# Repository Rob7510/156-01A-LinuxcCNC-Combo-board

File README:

Note: First version, in test.

This board can drive in LinuxCNC a 3-axis CNC over a single printer port set to default(out/epp) mode,
and provides 4 (pin 10-13) + 16 signal inputs and 9 (pin 1-9) + 16 output signals using the integrated
LSRIO16 softwaare multiplexer.

The X, Y, Z axis and A (or two other signals instead of A) are not isolated from the PC,
they connect to stepper drivers that are normally floating.
The remaining 20 input and 16 output signals are electrically isolated from the PC.

Combo port example configuration:

Pin Output Signal
1   Enable
2   X step
3   X dir
4   Y step
5   Y dir
6   Z step
7   Z dir
8   Spindle  etc
9   Aux out
14  LSRIO16 output (fixed onboard)
16  LSRIO16 clock (fixed onboard)
17  LSRIO16 data latch (fixed onboard)

Pin Input signal
10  X home
11  Y home
12  Z home
13  Probe
15  LSRIO16 input (fixed onboard)

All other signals (eg limits, ext_estop, buttons, lights) can be handled by the 16 in and 16
output signals of the LSRIO16 multimplexer with a polling delay of max 300 msec.

LSRIO16 fixed signal connections 
RCLK   <- SRIO-DATA_LATCH (P17)
SRCLK  <- SRIO-CLOCK-OUTPUT (P16)
DT-OUT -> LSRIO-INPUT-STREAM (P15)
DT-IN  <- SRIO-OUTPUT-STREAM (P14)
SRLD = inverted RCLK

Test software to set outputs and read inputs: mx16_test.hal, mx16_test.xml

updated 2024-10-17

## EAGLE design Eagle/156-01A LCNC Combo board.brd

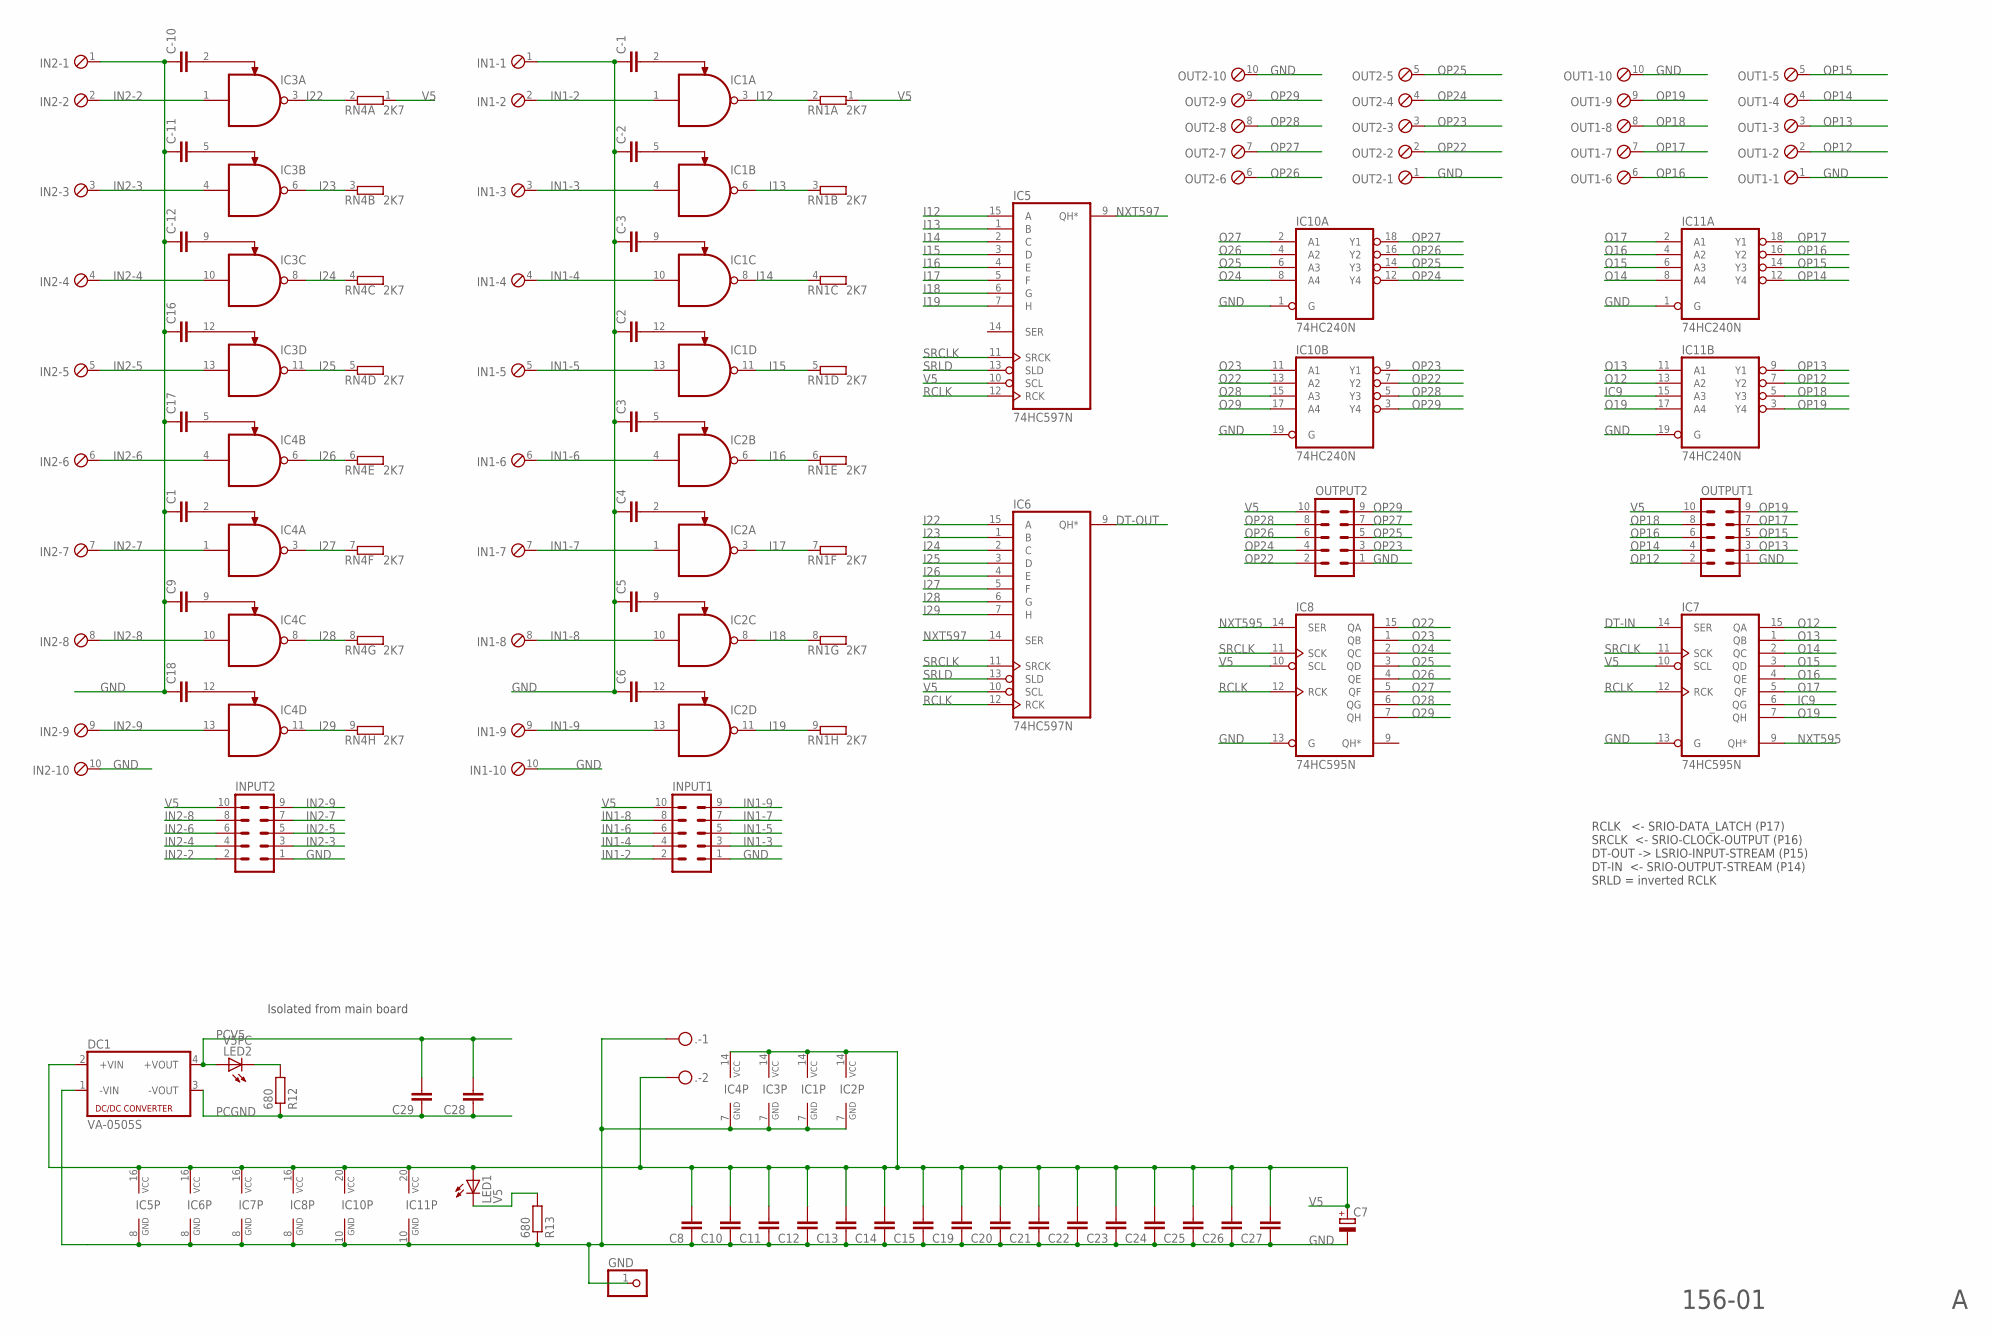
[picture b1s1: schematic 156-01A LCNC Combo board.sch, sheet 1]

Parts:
.: MKDSN1,5/2-5,08
C1, C2, C3, C4, C5, C6, C8, C9, C10, C11, C12, C13, C14, C15, C16, C17, C18, C19, C20, C21, C22, C23, C24, C25, C26, C27, C28, C29: C-EU025-024X044; C025-024X044
C7: CPOL-EUE3.5-8; E3,5-8
C-1, C-2, C-3, C-10, C-11, C-12: C-EU025-024X044; C025-024X044
DC1: VA-0505S; 4SIL
GND: PINHD-1X1; 1X01
IC1, IC2, IC3, IC4: MC1489DIP; DIL14
IC5, IC6: 74HC597N; DIL16
IC7, IC8: 74HC595N; DIL16
IC10, IC11: 74HC240N; DIL20
IN1, IN2: MPT10; 10POL254
INPUT1, INPUT2: ML10
LED1: V5; LED3MM
LED2: V5PC; LED3MM
OUT1, OUT2: MPT10; 10POL254
OUTPUT1, OUTPUT2: ML10
R12, R13: 680; 0207/10
RN1, RN4: 2K7; SIL9

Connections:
DT-IN: IC7.14 (SER); also elsewhere on the board
DT-OUT: IC6.9 (QH*); also elsewhere on the board
GND: ..1, C1.1, C2.1, C3.1, C4.1, C5.1, C6.1, C7.-, C8.1, C9.1, C10.1, C11.1, C12.1, C13.1, C14.1, C15.1, C16.1, C17.1, C18.1, C19.1, C20.1, C21.1, C22.1, C23.1, C24.1, C25.1, C26.1, C27.1, C-1.1, C-2.1, C-3.1, C-10.1, C-11.1, C-12.1, DC1.1 (-VIN), GND.1, IC1.7 (GND), IC2.7 (GND), IC3.7 (GND), IC4.7 (GND), IC5.8 (GND), IC6.8 (GND), IC7.8 (GND), IC7.13 (G), IC8.8 (GND), IC8.13 (G), IC10.1 (G), IC10.10 (GND), IC10.19 (G), IC11.1 (G), IC11.10 (GND), IC11.19 (G), IN1.1, IN1.10, IN2.1, IN2.10, INPUT1.1, INPUT2.1, OUT1.1, OUT1.10, OUT2.1, OUT2.10, OUTPUT1.1, OUTPUT2.1, R13.1; also elsewhere on the board
I12: IC1.3 (O), IC5.15 (A), RN1.2
I13: IC1.6 (O), IC5.1 (B), RN1.3 (2)
I14: IC1.8 (O), IC5.2 (C), RN1.4 (2)
I15: IC1.11 (O), IC5.3 (D), RN1.5 (2)
I16: IC2.6 (O), IC5.4 (E), RN1.6 (2)
I17: IC2.3 (O), IC5.5 (F), RN1.7 (2)
I18: IC2.8 (O), IC5.6 (G), RN1.8 (2)
I19: IC2.11 (O), IC5.7 (H), RN1.9 (2)
I22: IC3.3 (O), IC6.15 (A), RN4.2
I23: IC3.6 (O), IC6.1 (B), RN4.3 (2)
I24: IC3.8 (O), IC6.2 (C), RN4.4 (2)
I25: IC3.11 (O), IC6.3 (D), RN4.5 (2)
I26: IC4.6 (O), IC6.4 (E), RN4.6 (2)
I27: IC4.3 (O), IC6.5 (F), RN4.7 (2)
I28: IC4.8 (O), IC6.6 (G), RN4.8 (2)
I29: IC4.11 (O), IC6.7 (H), RN4.9 (2)
IC9: IC7.6 (QG), IC11.15 (A3)
IN1-2: IC1.1 (I0), IN1.2, INPUT1.2
IN1-3: IC1.4 (I0), IN1.3, INPUT1.3
IN1-4: IC1.10 (I0), IN1.4, INPUT1.4
IN1-5: IC1.13 (I0), IN1.5, INPUT1.5
IN1-6: IC2.4 (I0), IN1.6, INPUT1.6
IN1-7: IC2.1 (I0), IN1.7, INPUT1.7
IN1-8: IC2.10 (I0), IN1.8, INPUT1.8
IN1-9: IC2.13 (I0), IN1.9, INPUT1.9
IN2-2: IC3.1 (I0), IN2.2, INPUT2.2
IN2-3: IC3.4 (I0), IN2.3, INPUT2.3
IN2-4: IC3.10 (I0), IN2.4, INPUT2.4
IN2-5: IC3.13 (I0), IN2.5, INPUT2.5
IN2-6: IC4.4 (I0), IN2.6, INPUT2.6
IN2-7: IC4.1 (I0), IN2.7, INPUT2.7
IN2-8: IC4.10 (I0), IN2.8, INPUT2.8
IN2-9: IC4.13 (I0), IN2.9, INPUT2.9
unnamed: C-2.2, IC1.5 (I1)
unnamed: C-10.2, IC3.2 (I1)
unnamed: C17.2, IC4.5 (I1)
unnamed: C-3.2, IC1.9 (I1)
unnamed: C1.2, IC4.2 (I1)
unnamed: C9.2, IC4.9 (I1)
unnamed: C18.2, IC4.12 (I1)
unnamed: C2.2, IC1.12 (I1)
unnamed: C4.2, IC2.2 (I1)
unnamed: C5.2, IC2.9 (I1)
unnamed: C6.2, IC2.12 (I1)
unnamed: C-1.2, IC1.2 (I1)
unnamed: C3.2, IC2.5 (I1)
unnamed: LED2.K (C), R12.2
unnamed: LED1.K (C), R13.2
unnamed: C-11.2, IC3.5 (I1)
unnamed: C-12.2, IC3.9 (I1)
unnamed: C16.2, IC3.12 (I1)
NXT595: IC7.9 (QH*), IC8.14 (SER)
NXT597: IC5.9 (QH*), IC6.14 (SER)
O12: IC7.15 (QA), IC11.13 (A2)
O13: IC7.1 (QB), IC11.11 (A1)
O14: IC7.2 (QC), IC11.8 (A4)
O15: IC7.3 (QD), IC11.6 (A3)
O16: IC7.4 (QE), IC11.4 (A2)
O17: IC7.5 (QF), IC11.2 (A1)
O19: IC7.7 (QH), IC11.17 (A4)
O22: IC8.15 (QA), IC10.13 (A2)
O23: IC8.1 (QB), IC10.11 (A1)
O24: IC8.2 (QC), IC10.8 (A4)
O25: IC8.3 (QD), IC10.6 (A3)
O26: IC8.4 (QE), IC10.4 (A2)
O27: IC8.5 (QF), IC10.2 (A1)
O28: IC8.6 (QG), IC10.15 (A3)
O29: IC8.7 (QH), IC10.17 (A4)
OP12: IC11.7 (Y2), OUT1.2, OUTPUT1.2
OP13: IC11.9 (Y1), OUT1.3, OUTPUT1.3
OP14: IC11.12 (Y4), OUT1.4, OUTPUT1.4
OP15: IC11.14 (Y3), OUT1.5, OUTPUT1.5
OP16: IC11.16 (Y2), OUT1.6, OUTPUT1.6
OP17: IC11.18 (Y1), OUT1.7, OUTPUT1.7
OP18: IC11.5 (Y3), OUT1.8, OUTPUT1.8
OP19: IC11.3 (Y4), OUT1.9, OUTPUT1.9
OP22: IC10.7 (Y2), OUT2.2, OUTPUT2.2
OP23: IC10.9 (Y1), OUT2.3, OUTPUT2.3
OP24: IC10.12 (Y4), OUT2.4, OUTPUT2.4
OP25: IC10.14 (Y3), OUT2.5, OUTPUT2.5
OP26: IC10.16 (Y2), OUT2.6, OUTPUT2.6
OP27: IC10.18 (Y1), OUT2.7, OUTPUT2.7
OP28: IC10.5 (Y3), OUT2.8, OUTPUT2.8
OP29: IC10.3 (Y4), OUT2.9, OUTPUT2.9
PCGND: C28.1, C29.1, DC1.3 (-VOUT), R12.1; also elsewhere on the board
PCV5: C28.2, C29.2, DC1.4 (+VOUT), LED2.A; also elsewhere on the board
RCLK: IC5.12 (RCK), IC6.12 (RCK), IC7.12 (RCK), IC8.12 (RCK); also elsewhere on the board
SRCLK: IC5.11 (SRCK), IC6.11 (SRCK), IC7.11 (SCK), IC8.11 (SCK); also elsewhere on the board
SRLD: IC5.13 (SLD), IC6.13 (SLD); also elsewhere on the board
V5: ..2, C7.+, C8.2, C10.2, C11.2, C12.2, C13.2, C14.2, C15.2, C19.2, C20.2, C21.2, C22.2, C23.2, C24.2, C25.2, C26.2, C27.2, DC1.2 (+VIN), IC1.14 (VCC), IC2.14 (VCC), IC3.14 (VCC), IC4.14 (VCC), IC5.10 (SCL), IC5.16 (VCC), IC6.10 (SCL), IC6.16 (VCC), IC7.10 (SCL), IC7.16 (VCC), IC8.10 (SCL), IC8.16 (VCC), IC10.20 (VCC), IC11.20 (VCC), INPUT1.10, INPUT2.10, LED1.A, OUTPUT1.10, OUTPUT2.10, RN1.1, RN4.1; also elsewhere on the board

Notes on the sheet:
Isolated from main board
RCLK <- SRIO-DATA_LATCH (P17) SRCLK <- SRIO-CLOCK-OUTPUT (P16) DT-OUT -> LSRIO-INPUT-STREAM (P15) DT-IN <- SRIO-OUTPUT-STREAM (P14) SRLD = inverted RCLK
156-01

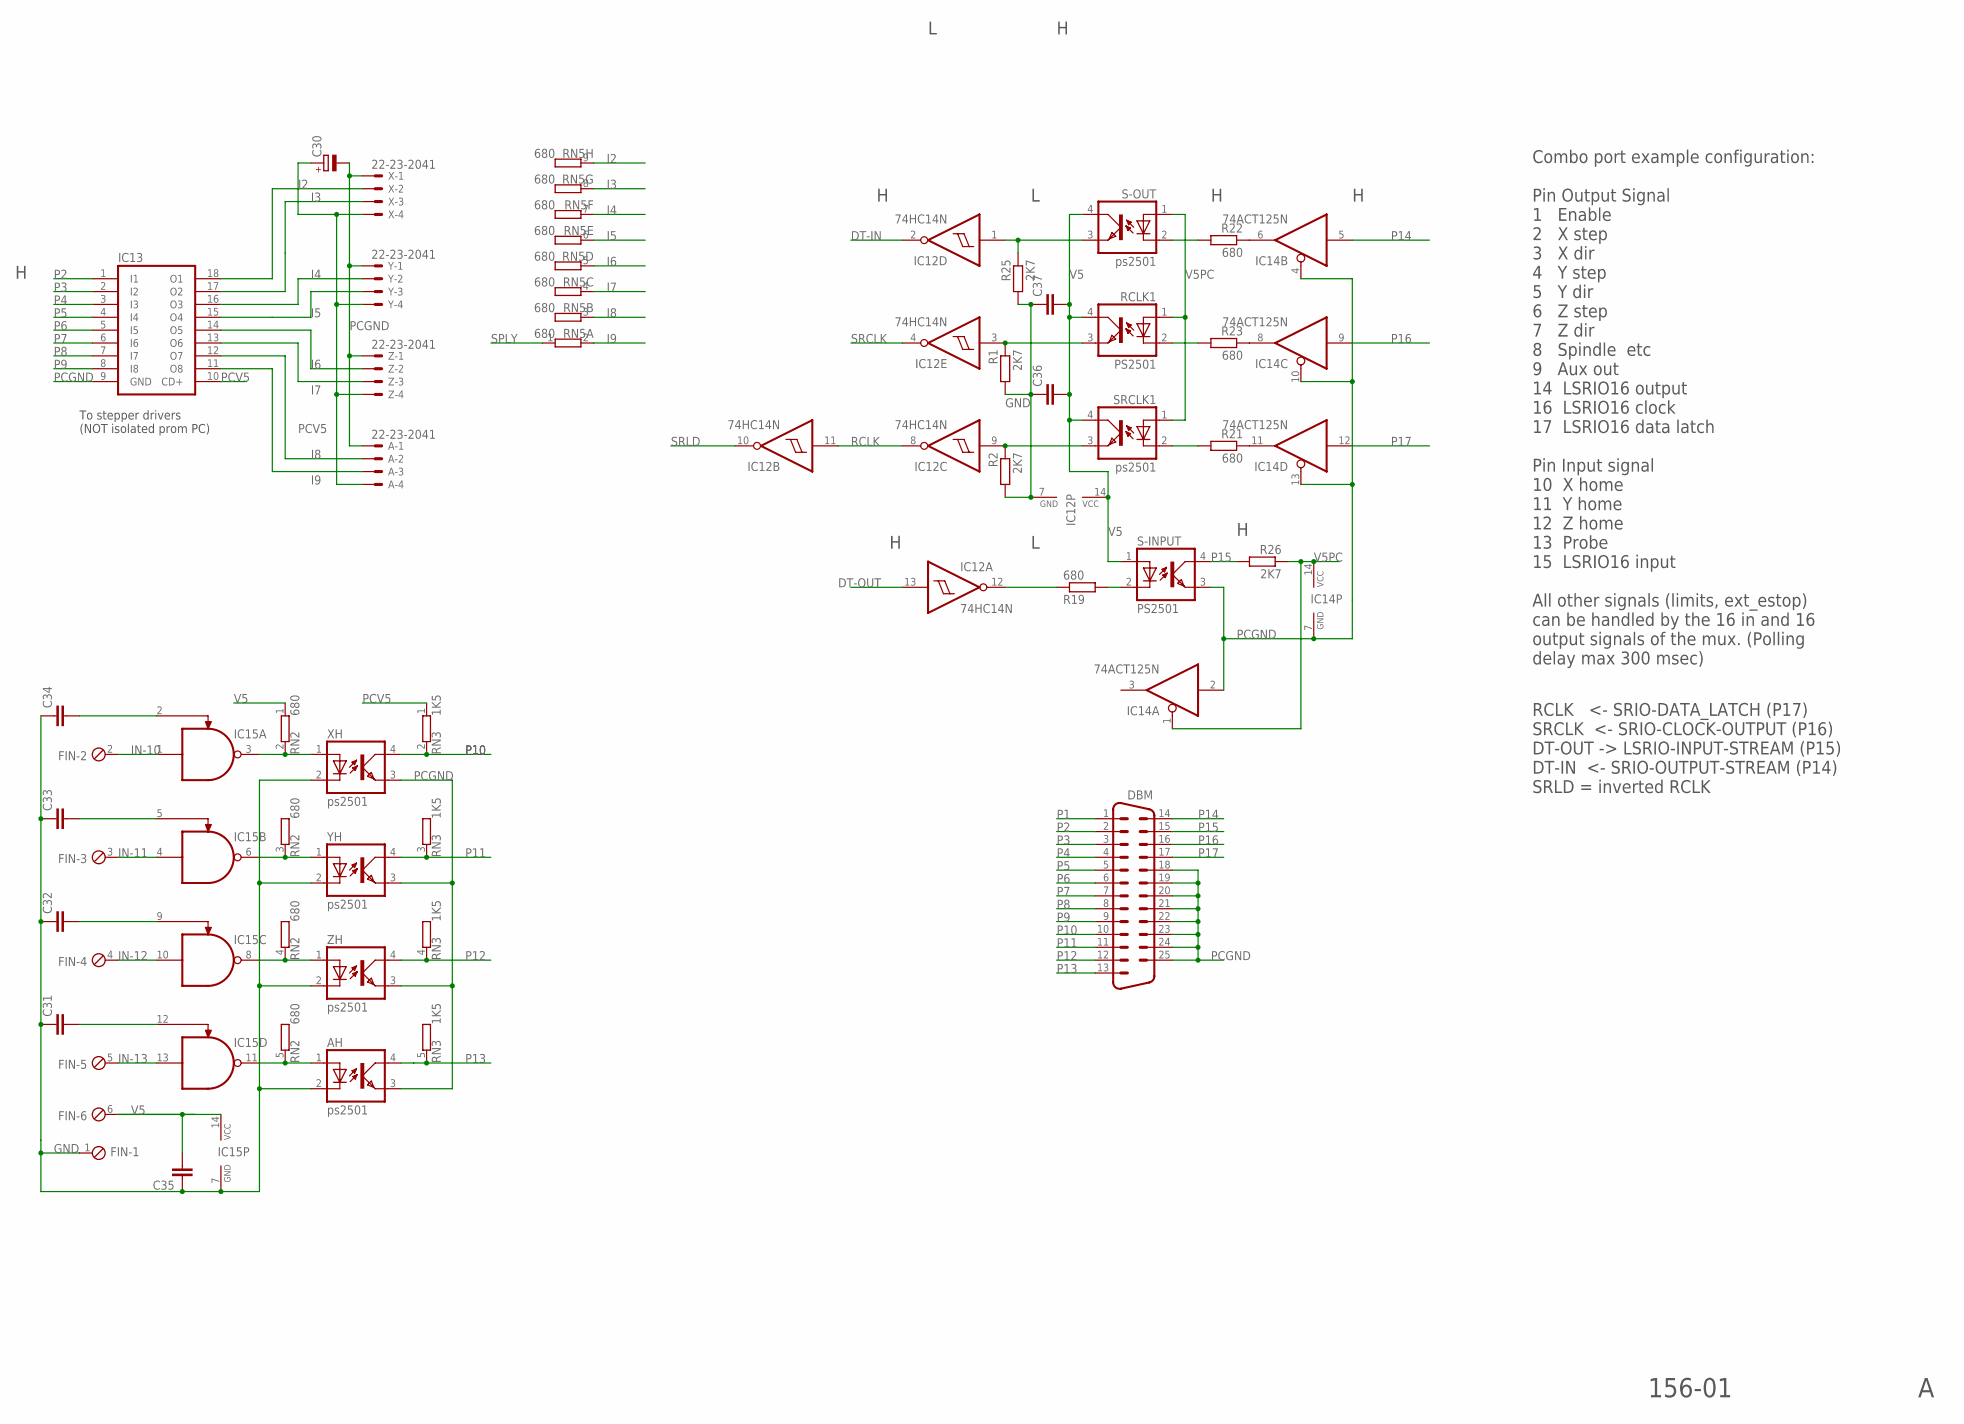
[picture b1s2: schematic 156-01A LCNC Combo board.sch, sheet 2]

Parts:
A: 22-23-2041
AH: ps2501; DIL04
C30: CPOL-EUE2.5-6; E2,5-6
C31, C32, C33, C34, C35, C36, C37: C-EU025-024X044; C025-024X044
DBM: M25HP
FIN: MPT6; 6POL254
IC12: 74HC14N; DIL14
IC13: ULN2803A; DIL18
IC14: 74ACT125N; DIL14
IC15: MC1489DIP; DIL14
R1, R2, R25, R26: 2K7; 0207/10
R19, R21, R22, R23: 680; 0207/10
RCLK1: PS2501; DIL04
RN2: 680; SIL5
RN3: 1K5; SIL5
RN5: 680; SIL9
S-INPUT: PS2501; DIL04
S-OUT: ps2501; DIL04
SRCLK1: ps2501; DIL04
X: 22-23-2041
XH: ps2501; DIL04
Y: 22-23-2041
YH: ps2501; DIL04
Z: 22-23-2041
ZH: ps2501; DIL04

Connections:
DT-IN: IC12.2 (O); also elsewhere on the board
DT-OUT: IC12.13 (I); also elsewhere on the board
GND: AH.2 (C), C31.1, C32.1, C33.1, C34.1, C35.1, C36.1, C37.1, FIN.1, IC12.7 (GND), IC15.7 (GND), R1.2, R2.2, R25.2, XH.2 (C), YH.2 (C), ZH.2 (C); also elsewhere on the board
I2: IC13.18 (O1), RN5.9 (2), X.2
I3: IC13.17 (O2), RN5.8 (2), X.3
I4: IC13.16 (O3), RN5.7 (2), Y.2
I5: IC13.15 (O4), RN5.6 (2), Y.3
I6: IC13.14 (O5), RN5.5 (2), Z.2
I7: IC13.13 (O6), RN5.4 (2), Z.3
I8: A.2, IC13.12 (O7), RN5.3 (2)
I9: A.3, IC13.11 (O8), RN5.2
IN-10: FIN.2, IC15.1 (I0)
IN-11: FIN.3, IC15.4 (I0)
IN-12: FIN.4, IC15.10 (I0)
IN-13: FIN.5, IC15.13 (I0)
unnamed: IC15.3 (O), RN2.2, XH.1 (A)
unnamed: IC14.6 (O), R22.1
unnamed: IC15.8 (O), RN2.4 (2), ZH.1 (A)
unnamed: AH.1 (A), IC15.11 (O), RN2.5 (2)
unnamed: C33.2, IC15.5 (I1)
unnamed: C34.2, IC15.2 (I1)
unnamed: C32.2, IC15.9 (I1)
unnamed: C31.2, IC15.12 (I1)
unnamed: IC15.6 (O), RN2.3 (2), YH.1 (A)
unnamed: R22.2, S-OUT.2 (C)
unnamed: IC12.3 (I), R1.1, RCLK1.3 (EMIT)
unnamed: R23.2, RCLK1.2 (C)
unnamed: IC12.1 (I), R25.1, S-OUT.3 (EMIT)
unnamed: IC12.9 (I), R2.1, SRCLK1.3 (EMIT)
unnamed: R21.2, SRCLK1.2 (C)
unnamed: IC12.12 (O), R19.1
unnamed: IC14.11 (O), R21.1
unnamed: IC14.8 (O), R23.1
unnamed: R19.2, S-INPUT.2 (C)
P1: DBM.1
P2: DBM.2, IC13.1 (I1)
P3: DBM.3, IC13.2 (I2)
P4: DBM.4, IC13.3 (I3)
P5: DBM.5, IC13.4 (I4)
P6: DBM.6, IC13.5 (I5)
P7: DBM.7, IC13.6 (I6)
P8: DBM.8, IC13.7 (I7)
P9: DBM.9, IC13.8 (I8)
P10: DBM.10, RN3.2, XH.4 (COL)
P11: DBM.11, RN3.3 (2), YH.4 (COL)
P12: DBM.12, RN3.4 (2), ZH.4 (COL)
P13: AH.4 (COL), DBM.13, RN3.5 (2)
P14: DBM.14, IC14.5 (I)
P15: DBM.15, R26.2, S-INPUT.4 (COL)
P16: DBM.16, IC14.9 (I)
P17: DBM.17, IC14.12 (I)
PCGND: A.1, AH.3 (EMIT), C30.-, DBM.18, DBM.19, DBM.20, DBM.21, DBM.22, DBM.23, DBM.24, DBM.25, IC13.9 (GND), IC14.2 (I), IC14.4 (OE), IC14.7 (GND), IC14.10 (OE), IC14.13 (OE), S-INPUT.3 (EMIT), X.1, XH.3 (EMIT), Y.1, YH.3 (EMIT), Z.1, ZH.3 (EMIT); also elsewhere on the board
PCV5: A.4, C30.+, IC13.10 (CD+), RN3.1, X.4, Y.4, Z.4; also elsewhere on the board
RCLK: IC12.8 (O), IC12.11 (I); also elsewhere on the board
SPLY: RN5.1
SRCLK: IC12.4 (O); also elsewhere on the board
SRLD: IC12.10 (O); also elsewhere on the board
V5: C35.2, C36.2, C37.2, FIN.6, IC12.14 (VCC), IC15.14 (VCC), RCLK1.4 (COL), RN2.1, S-INPUT.1 (A), S-OUT.4 (COL), SRCLK1.4 (COL); also elsewhere on the board
V5PC: IC14.1 (OE), IC14.14 (VCC), R26.1, RCLK1.1 (A), S-OUT.1 (A), SRCLK1.1 (A)

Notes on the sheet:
Combo port example configuration: Pin Output Signal 1 Enable 2 X step 3 X dir 4 Y step 5 Y dir 6 Z step 7 Z dir 8 Spindle etc 9 Aux out 14 LSRIO16 output 16 LSRIO16 clock 17 LSRIO16 data latch Pin Input signal 10 X home 11 Y home 12 Z home 13 Probe 15 LSRIO16 input All other signals (limits, ext_es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
To stepper drivers (NOT isolated prom PC)
RCLK <- SRIO-DATA_LATCH (P17) SRCLK <- SRIO-CLOCK-OUTPUT (P16) DT-OUT -> LSRIO-INPUT-STREAM (P15) DT-IN <- SRIO-OUTPUT-STREAM (P14) SRLD = inverted RCLK
156-01

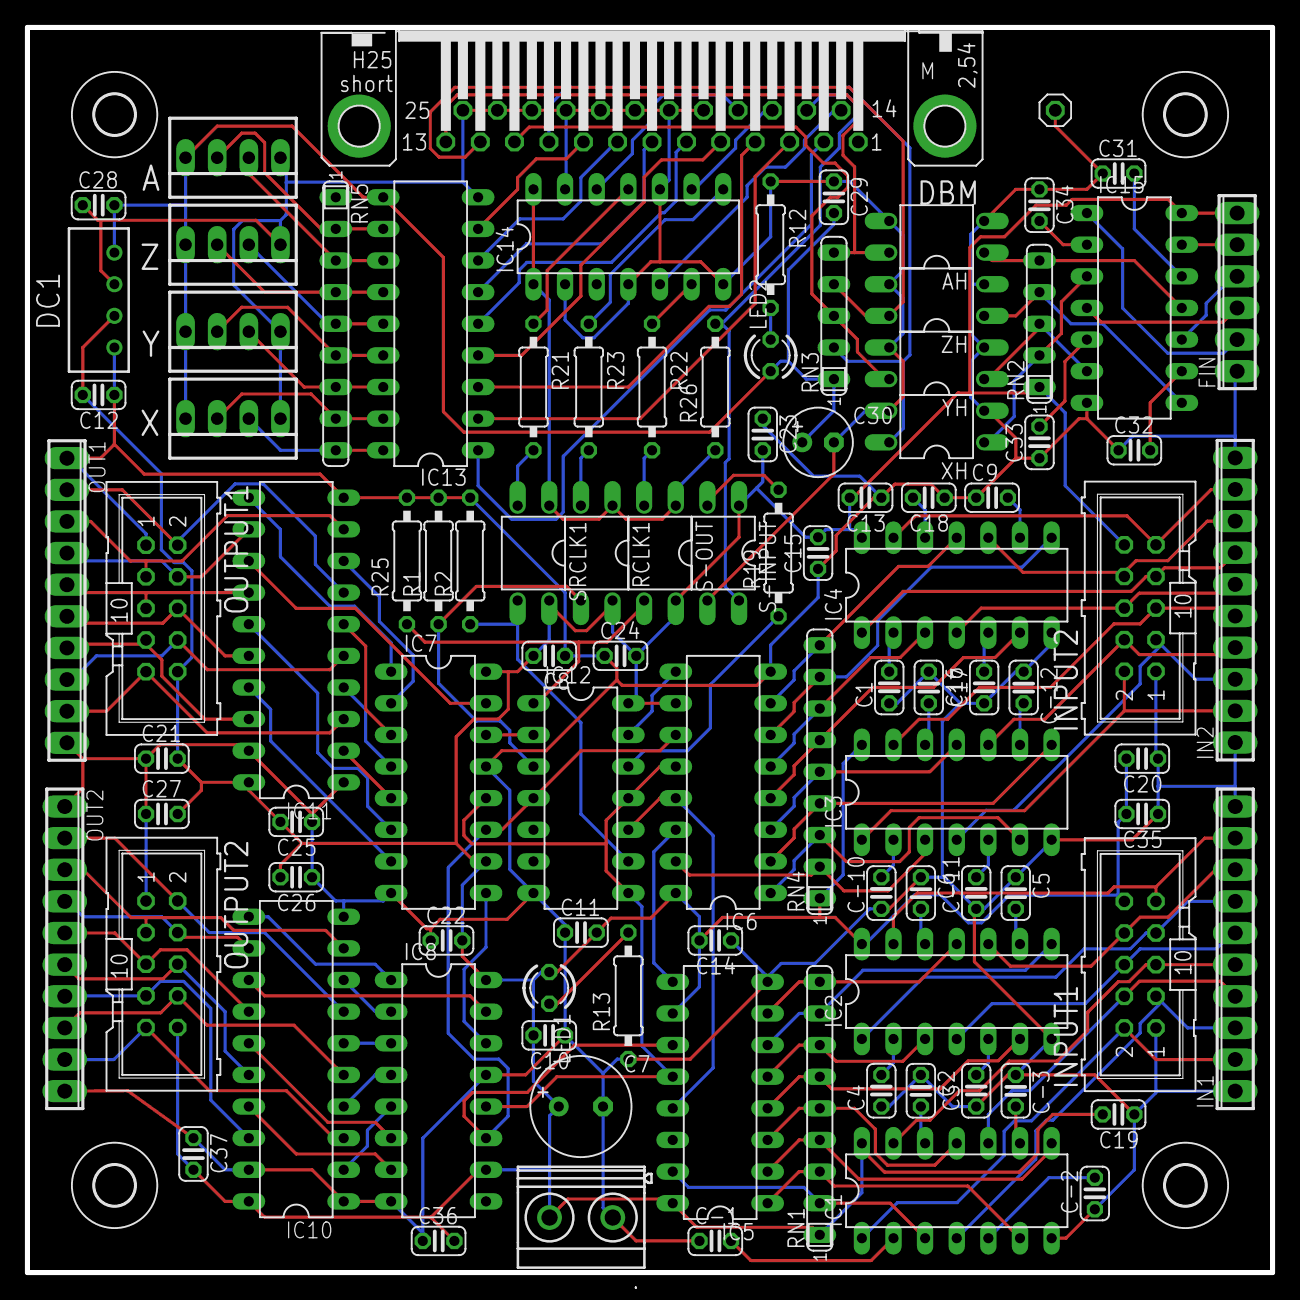
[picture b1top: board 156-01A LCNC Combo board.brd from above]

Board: 2 copper layers, 100.0 x 100.0 mm, 103 parts (0 on the bottom side), 141 nets.

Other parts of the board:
U$1, U$2, U$3, U$4: 3,2

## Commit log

2024-10-17 Added to the readme, removed random characters from a schematic drawing

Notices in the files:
Eagle/156-01A LCNC Combo board.brd:
License: CERN-OHL-P V2
